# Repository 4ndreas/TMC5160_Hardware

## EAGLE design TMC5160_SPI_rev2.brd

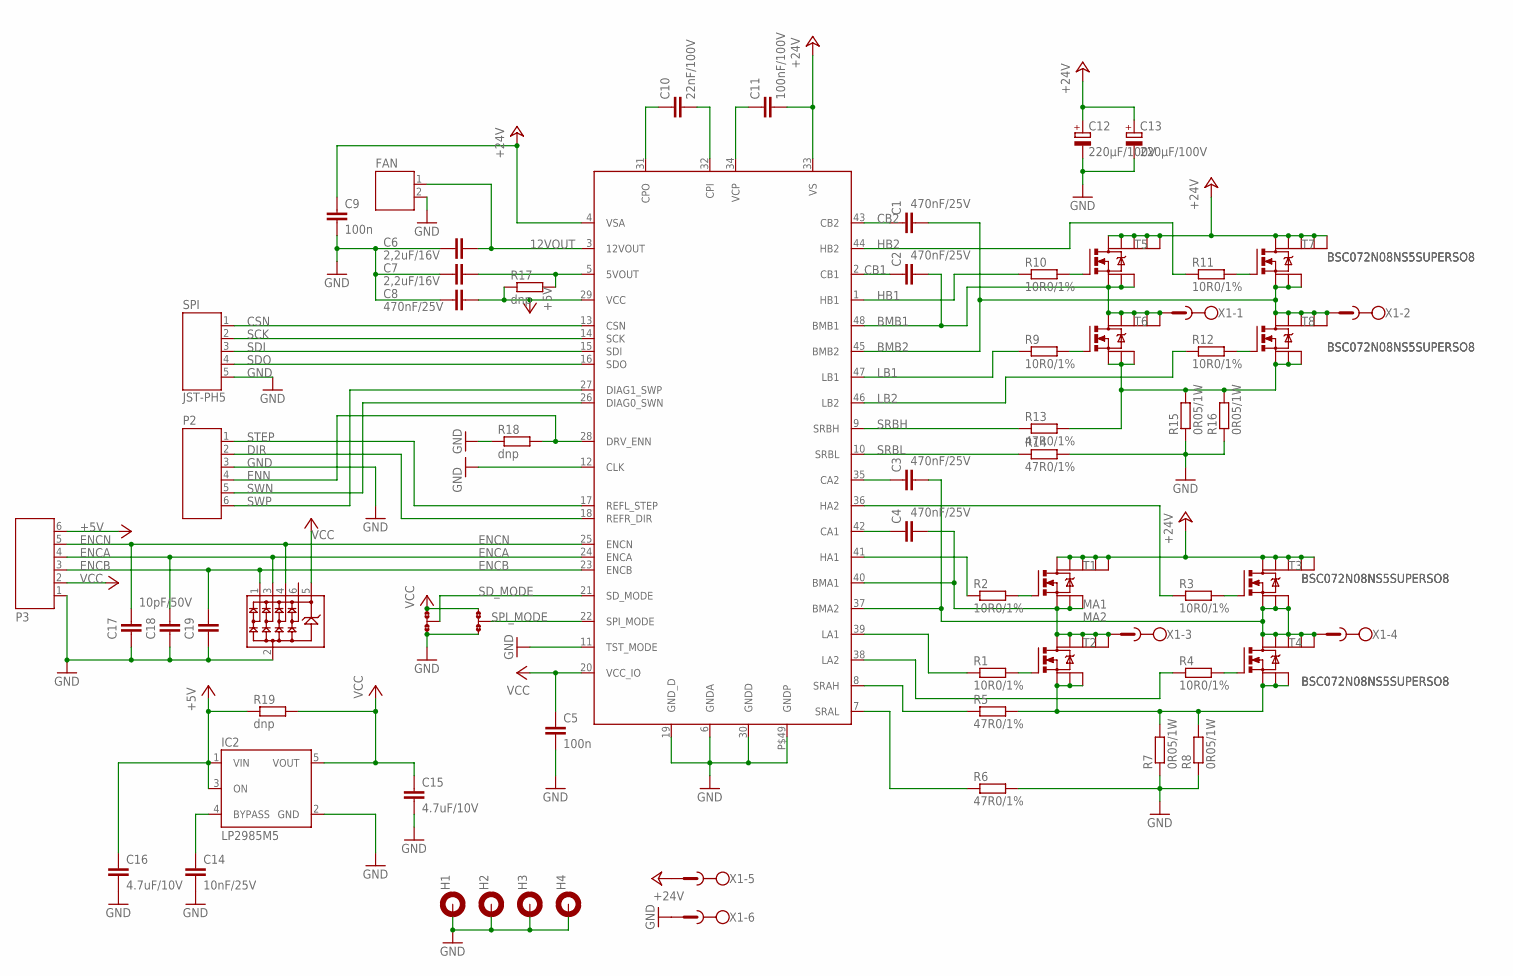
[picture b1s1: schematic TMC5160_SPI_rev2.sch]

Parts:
C1, C2, C3, C4, C8: 470nF/25V; C0805
C5, C9: 100n; C0603
C6, C7: 2,2uF/16V; C0805
C10: 22nF/100V; C0805
C11: 100nF/100V; C0805
C12, C13: 220µF/100V; 153CLV-1014
C14: 10nF/25V; C0603
C15, C16: 4.7uF/10V; C0603
C17, C18, C19: 10pF/50V; C0603
D1: SRV05-4SOT23-6-3D; SOT23-6
FAN: JST-PH2
H1, H2, H3, H4: MOUNT-PAD-ROUND3.2; 3,2-PAD
IC2: LP2985M5; SOT23-5
JMP1, JMP2: 0R-JUMPA; A0R-JMP
P2, P3: JST-PH6
R1, R2, R3, R4, R9, R10, R11, R12: 10R0/1%; R0603
R5, R6, R13, R14: 47R0/1%; R0603
R7, R8, R15, R16: 0R05/1W; R3225
R17, R18, R19: dnp; R0603
SPI: JST-PH5
T1, T2, T3, T4, T5, T6, T7, T8: BSC072N08NS5SUPERSO8; SOTFL127P615X110-8
TMC5160: TMC5160-TA; QFP50P900X900X120-48
X1: AKL166-06

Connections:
12VOUT: C6.2, FAN.1, TMC5160.3 (12VOUT)
+5V: C8.2, C16.1, IC2.1 (VIN), IC2.3 (ON), P3.6, R17.1, R19.1, TMC5160.29 (VCC)
+24V: C9.1, C11.2, C12.+, C13.+, T1.D, T1.D5 (D1), T1.D6 (D2), T1.D7 (D3), T1.D8 (D4), T3.D, T3.D5 (D1), T3.D6 (D2), T3.D7 (D3), T3.D8 (D4), T5.D, T5.D5 (D1), T5.D6 (D2), T5.D7 (D3), T5.D8 (D4), T7.D, T7.D5 (D1), T7.D6 (D2), T7.D7 (D3), T7.D8 (D4), TMC5160.4 (VSA), TMC5160.33 (VS), X1.5
BMB1: C2.2, T5.S1, T5.S2, T5.S3 (S), T6.D, T6.D5 (D1), T6.D6 (D2), T6.D7 (D3), T6.D8 (D4), TMC5160.48 (BMB1), X1.1
BMB2: C1.2, T7.S1, T7.S2, T7.S3 (S), T8.D, T8.D5 (D1), T8.D6 (D2), T8.D7 (D3), T8.D8 (D4), TMC5160.45 (BMB2), X1.2
CB1: C2.1, TMC5160.2 (CB1)
CB2: C1.1, TMC5160.43 (CB2)
CSN: SPI.1, TMC5160.13 (CSN)
DIR: P2.2, TMC5160.18 (REFR_DIR)
ENCA: C18.1, D1.3, P3.4, TMC5160.24 (ENCA)
ENCB: C19.1, D1.1, P3.3, TMC5160.23 (ENCB)
ENCN: C17.1, D1.4, P3.5, TMC5160.25 (ENCN)
ENN: P2.4, R18.2, TMC5160.28 (DRV_ENN)
GND: C5.2, C6.1, C7.2, C8.1, C9.2, C12.-, C13.-, C14.2, C15.2, C16.2, C17.2, C18.2, C19.2, D1.2, FAN.2, H1.B3,2, H2.B3,2, H3.B3,2, H4.B3,2, IC2.2 (GND), JMP1.3, JMP2.3, P2.3, P3.1, R6.2, R7.1, R8.1, R14.2, R15.1, R16.1, R18.1, SPI.5, TMC5160.6 (GNDA), TMC5160.11 (TST_MODE), TMC5160.12 (CLK), TMC5160.19 (GND_D), TMC5160.30 (GNDD), TMC5160.P$49 (GNDP), X1.6
HB1: R10.1, TMC5160.1 (HB1)
HB2: R11.1, TMC5160.44 (HB2)
LB1: R9.1, TMC5160.47 (LB1)
LB2: R12.1, TMC5160.46 (LB2)
MA1: C4.2, T1.S1, T1.S2, T1.S3 (S), T2.D, T2.D5 (D1), T2.D6 (D2), T2.D7 (D3), T2.D8 (D4), TMC5160.40 (BMA1), X1.3
MA2: C3.2, T3.S1, T3.S2, T3.S3 (S), T4.D, T4.D5 (D1), T4.D6 (D2), T4.D7 (D3), T4.D8 (D4), TMC5160.37 (BMA2), X1.4
unnamed: R1.2, T2.G
unnamed: R2.2, T1.G
unnamed: R3.2, T3.G
unnamed: R4.2, T4.G
unnamed: R5.2, R7.2, R8.2, T2.S1, T2.S2, T2.S3 (S), T4.S1, T4.S2, T4.S3 (S)
unnamed: R9.2, T6.G
unnamed: R10.2, T5.G
unnamed: R11.2, T7.G
unnamed: R12.2, T8.G
unnamed: R13.2, R15.2, R16.2, T6.S1, T6.S2, T6.S3 (S), T8.S1, T8.S2, T8.S3 (S)
unnamed: C4.1, TMC5160.42 (CA1)
unnamed: C3.1, TMC5160.35 (CA2)
unnamed: R3.1, TMC5160.36 (HA2)
unnamed: R4.1, TMC5160.38 (LA2)
unnamed: R1.1, TMC5160.39 (LA1)
unnamed: R2.1, TMC5160.41 (HA1)
unnamed: C14.1, IC2.4 (BYPASS)
unnamed: R5.1, TMC5160.8 (SRAH)
unnamed: R6.1, TMC5160.7 (SRAL)
unnamed: C7.1, R17.2, TMC5160.5 (5VOUT)
unnamed: C10.1, TMC5160.31 (CPO)
unnamed: C10.2, TMC5160.32 (CPI)
unnamed: C11.1, TMC5160.34 (VCP)
SCK: SPI.2, TMC5160.14 (SCK)
SDI: SPI.3, TMC5160.15 (SDI)
SDO: SPI.4, TMC5160.16 (SDO)
SD_MODE: JMP1.2, TMC5160.21 (SD_MODE)
SPI_MODE: JMP2.2, TMC5160.22 (SPI_MODE)
SRBH: R13.1, TMC5160.9 (SRBH)
SRBL: R14.1, TMC5160.10 (SRBL)
STEP: P2.1, TMC5160.17 (REFL_STEP)
SWN: P2.5, TMC5160.26 (DIAG0_SWN)
SWP: P2.6, TMC5160.27 (DIAG1_SWP)
VCC: C5.1, C15.1, D1.5, IC2.5 (VOUT), JMP1.1, JMP2.1, P3.2, R19.2, TMC5160.20 (VCC_IO)

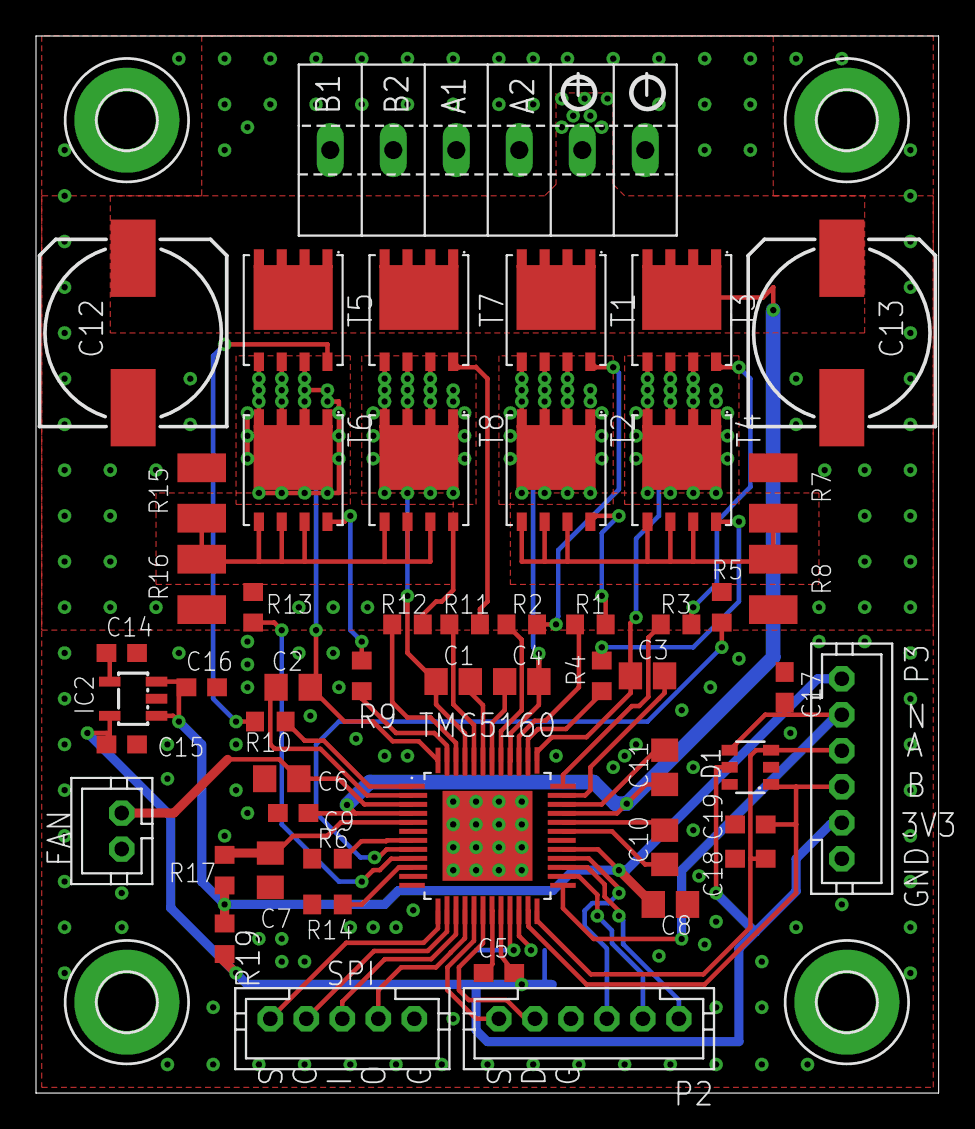
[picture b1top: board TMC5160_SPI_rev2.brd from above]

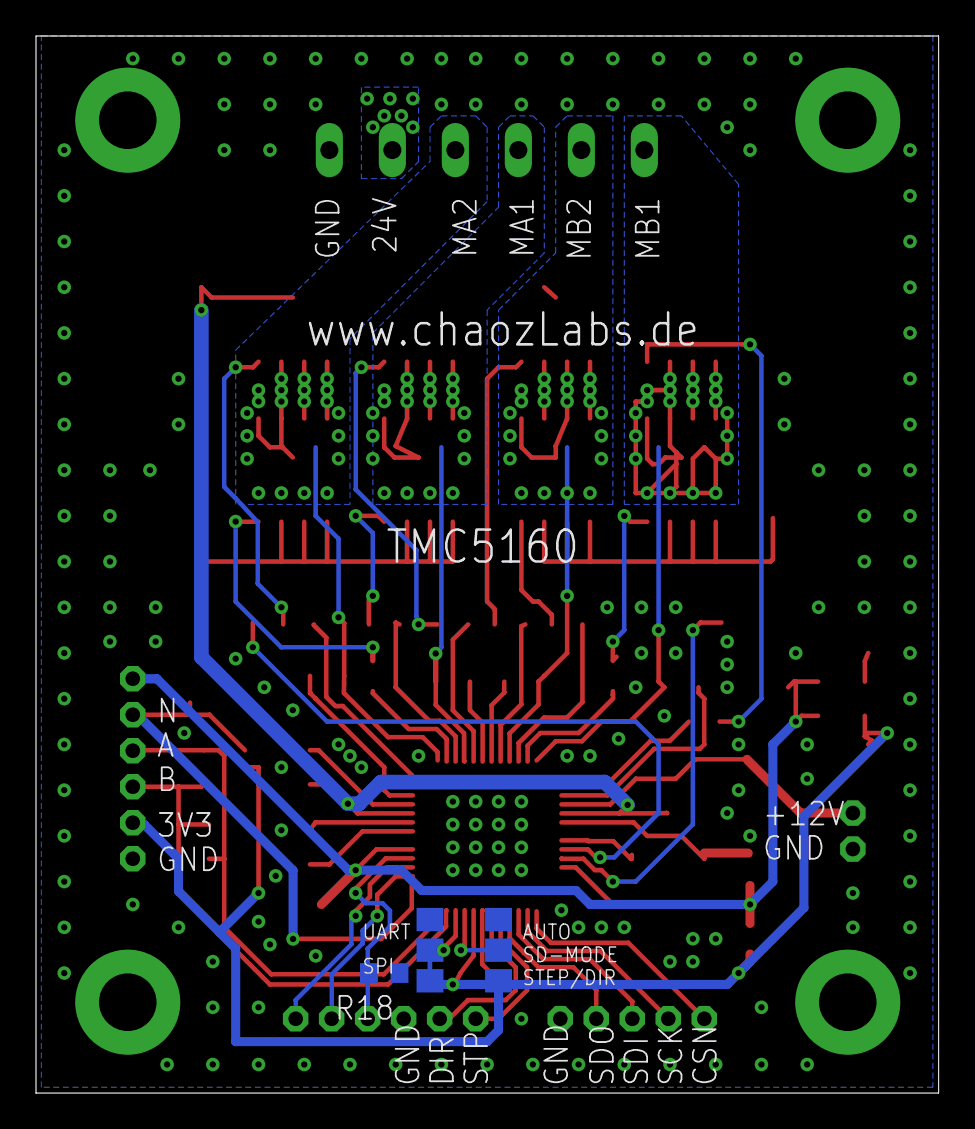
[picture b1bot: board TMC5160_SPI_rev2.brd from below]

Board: 2 copper layers, 50.1 x 58.7 mm, 60 parts (3 on the bottom side), 54 nets.

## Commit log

2019-06-12 first public release
